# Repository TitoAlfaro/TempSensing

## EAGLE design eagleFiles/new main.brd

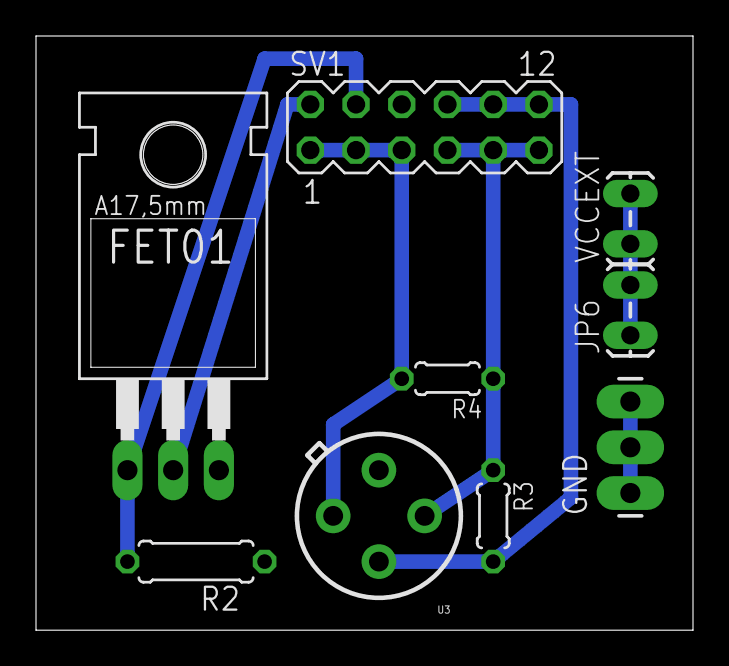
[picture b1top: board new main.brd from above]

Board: 2 copper layers, 36.5 x 33.0 mm, 9 parts (0 on the bottom side), 7 nets.

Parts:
FET01: IRF3710; TO220AH
GND: 1X03_LONGPADS
JP6: 1X02_LOCK_LONGPADS
R2: 10k; 0207/7
R3, R4: 4.1k; 0204/5
SV1: MA06-2
U3: MLX90614_; TO-39
VCCEXT: 1X02_LOCK_LONGPADS

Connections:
GND: FET01.E, GND.1, GND.2, GND.3, R2.1, U3.4
unnamed: JP6.1, JP6.2, VCCEXT.1, VCCEXT.2
unnamed: FET01.C, SV1.2
unnamed: R4.2, SV1.1, SV1.3, SV1.5, U3.1
unnamed: R3.2, SV1.8, SV1.10, SV1.12, U3.2
unnamed: FET01.B, R2.2, SV1.4
VCC3: R3.1, R4.1, SV1.7, SV1.9, SV1.11, U3.3

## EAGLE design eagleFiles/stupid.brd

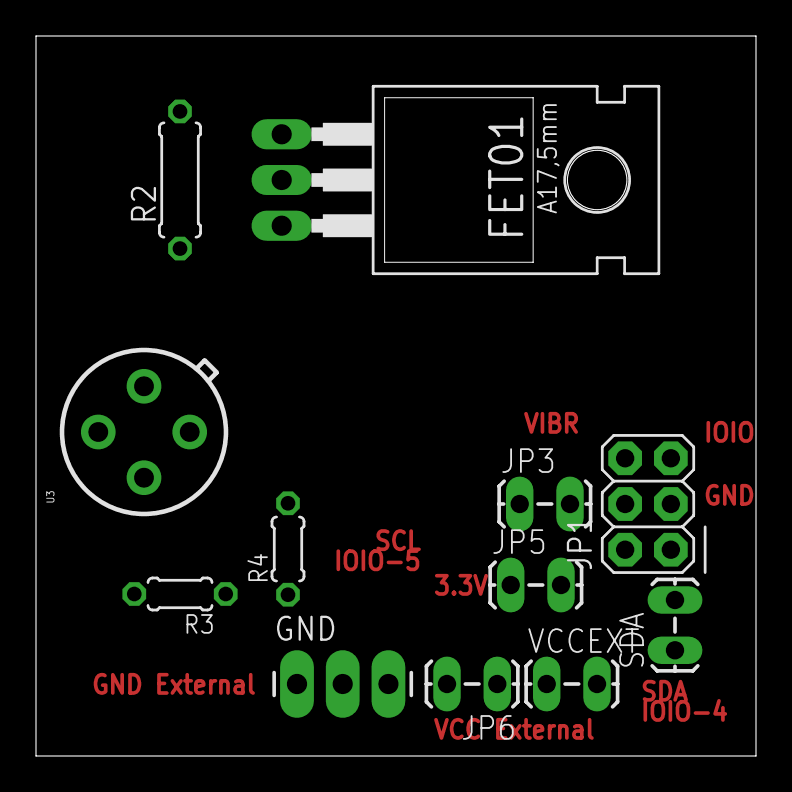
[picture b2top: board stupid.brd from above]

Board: 2 copper layers, 40.0 x 40.0 mm, 12 parts (0 on the bottom side), 7 nets, no tracks yet.

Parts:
FET01: IRF3710; TO220AH
GND: 1X03_LONGPADS
JP1: 2X03
JP3, JP5, JP6: 1X02_LOCK_LONGPADS
R2: 10k; 0207/7
R3, R4: 4.1k; 0204/5
SDA: 1X02_LOCK_LONGPADS
U3: MLX90614_; TO-39
VCCEXT: 1X02_LOCK_LONGPADS

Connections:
GND: FET01.E, GND.1, GND.2, GND.3, JP1.3, R2.1, U3.4
unnamed: JP6.1, JP6.2, VCCEXT.1, VCCEXT.2
unnamed: FET01.C, JP1.6
unnamed: JP1.4, JP3.1, JP3.2, R4.2, U3.1
unnamed: JP1.1, R3.2, SDA.1, SDA.2, U3.2
unnamed: FET01.B, JP1.5, R2.2
VCC3: JP1.2, JP5.1, JP5.2, R3.1, R4.1, U3.3

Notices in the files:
parts and their libraries:
SparkFun-Sensors: Licensing: CC v3.0 Share-Alike You are welcome to use this library for commercial purposes.
